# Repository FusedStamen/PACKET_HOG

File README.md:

# PACKET_HOG

10-node ESP32-C5 scanner carrier board. One master, a bank of scan nodes, single USB-C power in.

Status: **PacketHog-V2 first batch is sold out. A restock order has been placed** (no firm arrival date, no preorders; the store page reopens when boards are in hand). V1 (first batch of 8) is also sold out. Every V2 board is assembled and checked before it ships.

## What it is

Packet Hog C5 is a carrier board built around the Seeed XIAO ESP32-C5. One master node coordinates a bank of scanner nodes over ESP-NOW, each scanning dual-band Wi-Fi (2.4/5 GHz) and BLE. The whole array runs off a single USB-C input.

Built deliberately barebones with power distribution, node bank, antenna breakout, nothing else.

Board size: 183.7mm x 121.1mm (7.23 x 4.77 in), 1.6mm thick. Standard case: 188.1mm x 125.5mm, about 29mm tall. Fan case: about 45.5mm tall.

## Buy it

PacketHog-V2: **$100**, shipping to the US only right now. Same price for every option. **Currently sold out, restock ordered.** Restock alert signup: [tally.so/r/Z9Elga](https://tally.so/r/Z9Elga)

[fusedstamen.com/packethogv2](https://fusedstamen.com/packethogv2)

Options at checkout when available: soldered RP-SMA connectors, or bare board (as received from assembly, SMA positions empty). Every board comes with the standard printed case. A case with a 30mm fan opening is available to print from this repo if you want one. Name and Discord are optional at checkout; I only need a shipping address and email.

Modules (Seeed XIAO ESP32-C5), antennas and fan not included. Outside the US, message me on Discord first - import VAT, duties and carrier fees are paid by the buyer on delivery.

## Case hardware

- Standard case: 4x M3x25 screws into M3 heat-set inserts.
- Fan case lid: 4x M3x40 (about 2.5mm of thread engagement; use M3x45 if it feels loose).
- Fan: 5V, 2-pin, 30mm. Check the fan thickness against the fan case. Fan screws are 2-4x M3x8 to M3x10 self-tapping. Specific fans are untested.

**Note on the RP-SMA connectors (J1-J10):** they're mounted to the board for physical support only - there's no PCB trace routing antenna signal to them. Each node module's signal reaches its SMA connector through a short U.FL-to-RP-SMA pigtail from the module itself, not through the board's copper. Same setup as the Piglet, in case that's caused confusion before.

**Mounting orientation:** every header position follows the same rule. Seat each XIAO module so its USB-C port faces the same side as the nearby capacitor (e.g. C11 sits next to the H1A/H1B pair) - that side matches the direction the onboard USB-C (J11) faces. The module's U.FL antenna pad ends up on the opposite side. Get this backwards and the module won't seat or power on correctly; double check before powering on.

## Version history

- **Prototype 1** - First routed prototype. Had a wiring mistake around the CH224K USB-C PD negotiation chip: on a "smart" PD-negotiating charger, the board could get handed the wrong voltage, which risked damaging the nodes. Safe with plain 5V "dumb" chargers only.
- **Prototype 2** - CH224K removed entirely; replaced with 5.1kΩ pull-down resistors on CC1/CC2, forcing 5V-default behavior regardless of charger. Also added reverse-polarity protection, a fuse at the power input, bulk + per-node decoupling capacitors, and 10 edge-mounted SMA connectors for external antennas. Had a layout flaw: SMA connector mounts sat too close to the header pins, leaving insufficient clearance to hand-solder/route pigtail connections without crowding the header footprints. Also shipped without mounting holes, so boards couldn't be securely fastened into a case.
- **PacketHog-V1** - Fixes the clearance flaw by widening the board (77.1mm to 121.1mm) to give proper spacing between the SMA connectors and the header rows. Added M3 mounting holes. Rounded board corners. SMA connectors hand-soldered (not PCBA-populated). First batch of 8 sold out.
- **PacketHog-V2** - Current revision. Power traces widened from 0.5mm to 1.0mm (the USB-C-to-fuse run is limited by the connector pad width). Added a 2-pin fan header (5V + GND, factory assembled). Added an AUX 5V/GND through-hole header, unpopulated, same pinout as the fan header (square pad GND, round pad +5V). Added 7 labelled test points: USB input voltage, between fuse and diode, 5V rail, far-end 5V, and 3x GND. Silkscreen cleanup; back label says V2. Power parts unchanged from V1. Still hand-soldered through-hole RP-SMA (mechanical only), plain USB-C 5V with no PD, 3A maximum (PTC fuse, fan counts against it).
- **Planned for V3** - Power switch, power LED, onboard U.FL plus edge SMA, battery input, possibly 4-layer.

**Known issue:** some nodes drop out with certain off-brand USB cables or power banks. Cause not yet measured; V2 does not claim to fix it. Use a decent USB-C cable and a supply that can deliver 5V at 3A.

## Status of what's tested

| Component | Status |
|---|---|
| Power distribution | Tested |
| Fully populated board scanning | Tested |
| PacketHog-V1 board fab/assembly | Tested |
| PacketHog-V2 board fab/assembly | Tested (each board checked before shipping) |
| Fan case (30mm) | Complete, files in this repo |
| Antenna path (module -> U.FL/SMA pigtail) | Tested |

## Thermal notes

I ran a thermal test on a V1 board in a closed case in a room at about 78F (25.5C). After 75+ minutes of running, the air inside the case levelled off around 96F (36C) and the nodes measured about 102-110F (39-43C) with a thermocouple. An IR thermometer read higher, 108-118F (42-48C), which is typical of IR on shiny surfaces, so treat the thermocouple numbers as the more reliable set. The test was on V1; V2 uses the same power parts with wider copper.

For reference, Espressif rates the ESP32-C5 modules for an operating ambient temperature of -40C to 85C (185F). The Seeed XIAO ESP32-C5 board is listed at 0C to 85C. Nodes ran well inside that range in my test, so I don't think a fan is necessary. The fan header and fan case are there if you want extra airflow or plan to run in a hot environment, such as a car parked in the sun. Those limits are ambient ratings, so a very hot environment leaves less margin.

Test data: [Packet_Hog-v1-Thermal_Testing.xlsx](./Packet_Hog-v1-Thermal_Testing.xlsx)

## License

Licensed under **CC BY-NC 4.0** - see [LICENSE](./LICENSE) for full terms.

Short version: you're free to build one for yourself and modify it for personal, non-commercial use. Selling anything built from this design - boards, kits, or products - requires explicit permission from me first. See the LICENSE file for exactly what that means.

## Contact

- Discord: `Fusedstamen`
- GitHub: [github.com/FusedStamen](https://github.com/FusedStamen)

If you want to use this commercially, reach out through one of the above. Don't assume permission - wait for a yes.

## Name

"Packet Hog" - a reference to [Bilmuri](https://bilmuri.com), not a fork or rename of anyone else's project.

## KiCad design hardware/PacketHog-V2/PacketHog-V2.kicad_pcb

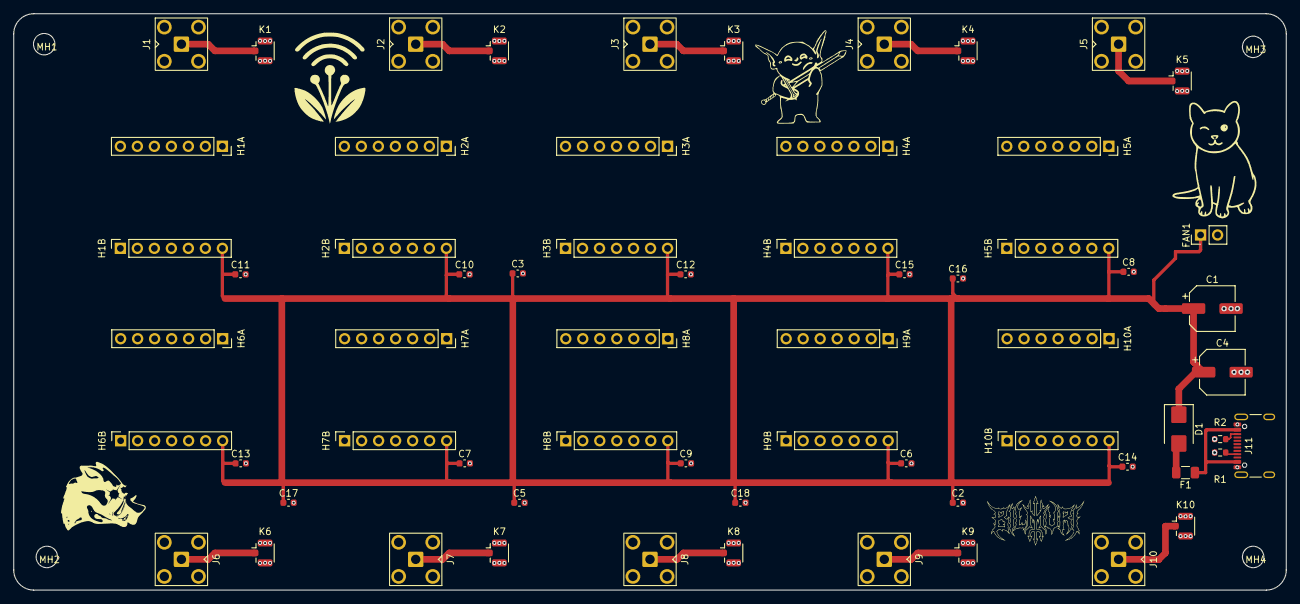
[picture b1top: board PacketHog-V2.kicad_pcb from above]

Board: 2 copper layers, 190.1 x 86.1 mm, 68 parts (0 on the bottom side), 16 nets.

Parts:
C1, C4: CP_Elec_6.3x5.4
C2, C3, C5, C16, C17, C18: 1uF; C_0603_1608Metric
C6, C7, C8, C9, C10, C11, C12, C13, C14, C15: 10uF; C_0603_1608Metric
D1: D_SMB
F1: Fuse_1206_3216Metric
FAN1: PinHeader_1x02_P2.54mm_Vertical
H1A, H1B, H2A, H2B, H3A, H3B, H4A, H4B, H5A, H5B, H6A, H6B, H7A, H7B, H8A, H8B, H9A, H9B, H10A, H10B: PinSocket_1x07_P2.54mm_Vertical
J1, J2, J3, J4, J5, J6, J7, J8, J9, J10: SMA_BAT_Wireless_BWSMA-KWE-Z001
J11: USB_C_Receptacle_GCT_USB4105; USB_C_Receptacle_GCT_USB4105-xx-A_16P_TopMnt_Horizontal
K1, K2, K3, K4, K5, K6, K7, K8, K9, K10: U.FL_Hirose_U.FL-R-SMT-1_Vertical
MH1, MH2, MH3, MH4: MountingHole_3.2mm_M3
R1, R2: 5.1k; R_0603_1608Metric

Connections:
+5V: C1.1, C2.1, C3.1, C4.1, C5.1, C6.1, C7.1, C8.1, C9.1, C10.1, C11.1, C12.1, C13.1, C14.1, C15.1, C16.1, C17.1, C18.1, D1.1, FAN1.1, H1B.7, H2B.7, H3B.7, H4B.7, H5B.7, H6B.7, H7B.7, H8B.7, H9B.7, H10B.7
CC1: J11.B5, R2.2
CC2: J11.A5, R1.2
F1_OUT: D1.2, F1.2
GND: C1.2, C2.2, C3.2, C4.2, C5.2, C6.2, C7.2, C8.2, C9.2, C10.2, C11.2, C12.2, C13.2, C14.2, C15.2, C16.2, C17.2, C18.2, FAN1.2, H1B.6, H2B.6, H3B.6, H4B.6, H5B.6, H6B.6, H7B.6, H8B.6, H9B.6, H10B.6, J1.2, J2.2, J3.2, J4.2, J5.2, J6.2, J7.2, J8.2, J9.2, J10.2, J11.A1, J11.A12, J11.B1, J11.B12, J11.SH, K1.2, K2.2, K3.2, K4.2, K5.2, K6.2, K7.2, K8.2, K9.2, K10.2, R1.1, R2.1
SMA1: J1.1, K1.1
SMA2: J2.1, K2.1
SMA3: J3.1, K3.1
SMA4: J4.1, K4.1
SMA5: J5.1, K5.1
SMA6: J6.1, K6.1
SMA7: J7.1, K7.1
SMA8: J8.1, K8.1
SMA9: J9.1, K9.1
SMA10: J10.1, K10.1
VBUS: F1.1, J11.A4, J11.A9, J11.B4, J11.B9

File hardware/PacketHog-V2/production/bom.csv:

Designator,Footprint,Quantity,Value,LCSC Part #
"C1, C4",CP_Elec_6.3x5.4,2,CP_Elec_6.3x5.4,
"C10, C11, C12, C13, C14, C15, C6, C7, C8, C9",0603,10,10uF,
"C16, C17, C18, C2, C3, C5",0603,6,1uF,
D1,D_SMB,1,D_SMB,
F1,1206,1,Fuse_1206_3216Metric,
FAN1,PinHeader_1x02_P2.54mm_Vertical,1,PinHeader_1x02_P2.54mm_Vertical,
"H10A, H10B, H1A, H1B, H2A, H2B, H3A, H3B, H4A, H4B, H5A, H5B, H6A, H6B, H7A, H7B, H8A, H8B, H9A, H9B",PinSocket_1x07_P2.54mm_Vertical,20,PinSocket_1x07_P2.54mm_Vertical,
"J1, J10, J2, J3, J4, J5, J6, J7, J8, J9",SMA_BAT_Wireless_BWSMA-KWE-Z001,10,SMA_BAT_Wireless_BWSMA-KWE-Z001,
J11,USB_C_Receptacle_GCT_USB4105-xx-A_16P_TopMnt_Horizontal,1,USB_C_Receptacle_GCT_USB4105,
"K1, K10, K2, K3, K4, K5, K6, K7, K8, K9",U.FL_Hirose_U.FL-R-SMT-1_Vertical,10,U.FL_Hirose_U.FL-R-SMT-1_Vertical,
"R1, R2",0603,2,5.1k,

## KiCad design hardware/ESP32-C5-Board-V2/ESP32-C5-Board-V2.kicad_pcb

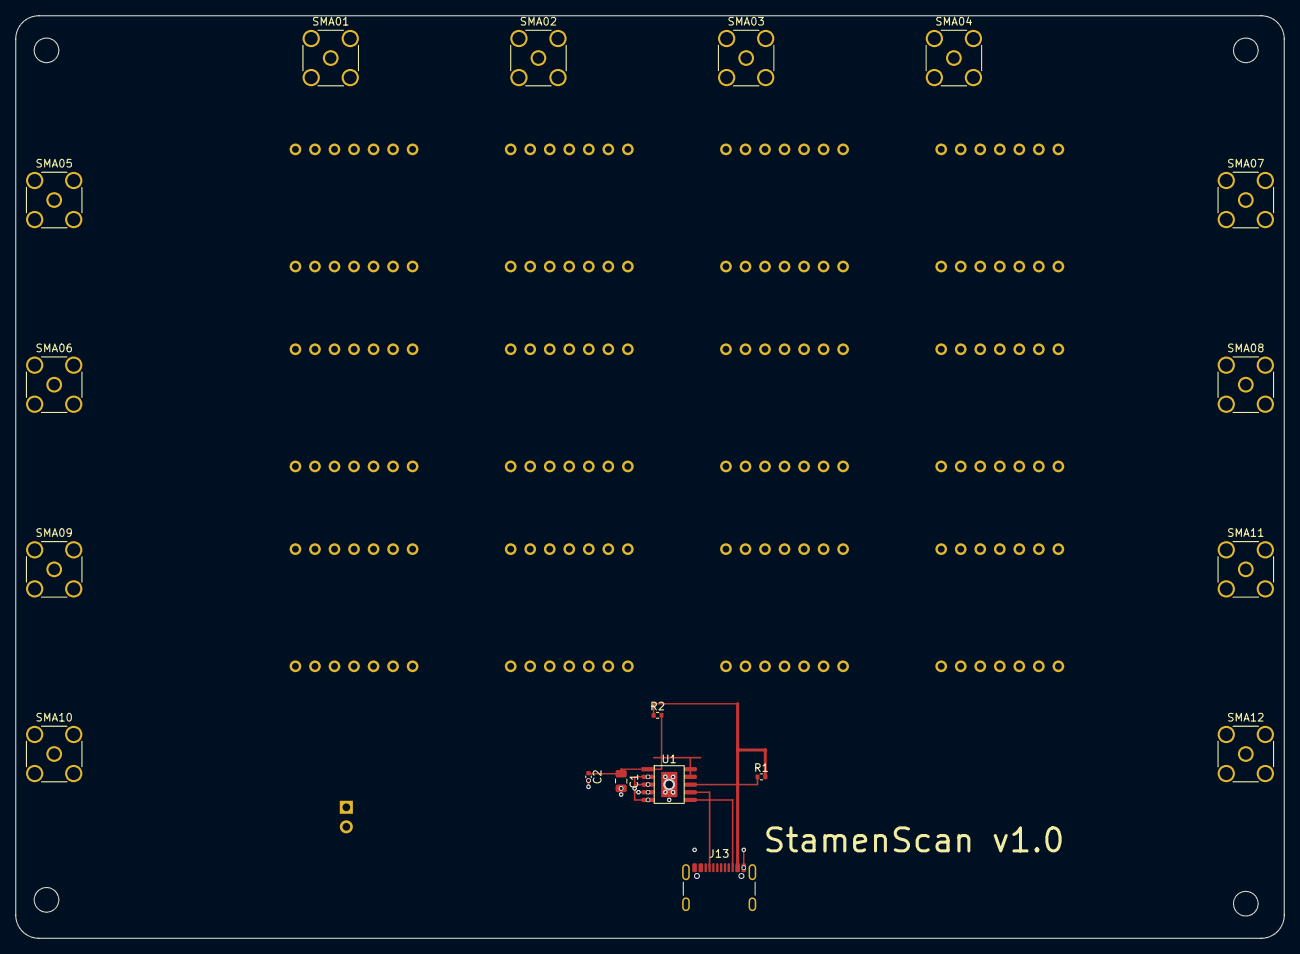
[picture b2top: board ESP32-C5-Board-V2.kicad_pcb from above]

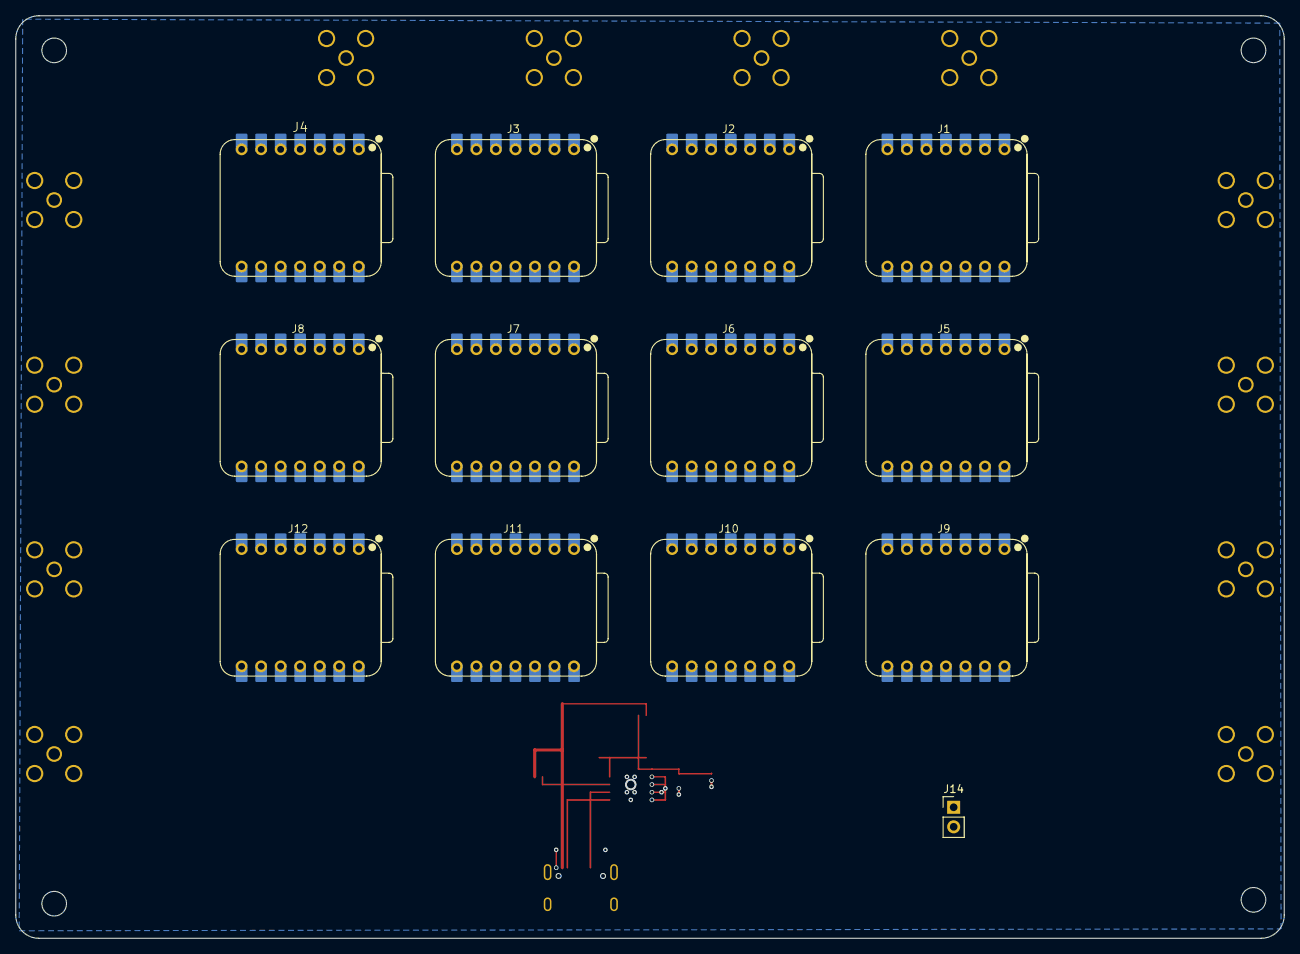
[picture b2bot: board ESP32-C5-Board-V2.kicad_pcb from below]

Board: 2 copper layers, 165.0 x 120.0 mm, 35 parts (17 on the bottom side), 5 nets.

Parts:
C1: 100nF; C_0805_2012Metric
C2: 10uF; C_0402_1005Metric
J1, J2, J3, J4, J5, J6, J7, J8, J9, J10, J11, J12: XIAO-ESP32-C5; XIAO-ESP32-C5-DIP
J13: USB_C_PWR_IN; USB_C_Receptacle_GCT_USB4105-xx-A_16P_TopMnt_Horizontal
J14: FAN; PinHeader_1x02_P2.54mm_Vertical
MH1, MH2, MH3, MH4: MountingHole_3.2mm
R1: 10k; R_0402_1005Metric
R2: 1k; R_0402_1005Metric
SMA01, SMA02, SMA03, SMA04, SMA05, SMA06, SMA07, SMA08, SMA09, SMA10, SMA11, SMA12: SMA_Amphenol_132291_Vertical
U1: CH224K; CH224K_ESSOP-10

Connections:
+5V: J1.14 (VBUS), J2.14 (VBUS), J3.14 (VBUS), J4.14 (VBUS), J5.14 (VBUS), J6.14 (VBUS), J7.14 (VBUS), J8.14 (VBUS), J9.14 (VBUS), J10.14 (VBUS), J11.14 (VBUS), J12.14 (VBUS), J13.A4, J13.A9, J13.B4, J13.B9, J14.1 (+5V), R1.1, R1.2, R2.1, U1.8
CC1: J13.A5 (CC1), U1.7
CC2: J13.B5 (CC2), U1.6
GND: C1.2, C2.2, J1.13 (GND), J2.13 (GND), J3.13 (GND), J4.13 (GND), J5.13 (GND), J6.13 (GND), J7.13 (GND), J8.13 (GND), J9.13 (GND), J10.13 (GND), J11.13 (GND), J12.13 (GND), J13.A1 (VBUS), J13.A12 (GND), J13.B1 (VBUS), J13.B12 (GND), J14.2 (GND), U1.0, U1.2, U1.3, U1.4, U1.5
VDD: C1.1, C2.1, R2.2, U1.1, U1.9, U1.10

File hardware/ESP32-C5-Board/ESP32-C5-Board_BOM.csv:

value,footprint,quantity,references
10k,Resistor_SMD:R_0402_1005Metric,3,"['R1', 'R2', 'R3']"
FAN,Connector_PinHeader_2.54mm:PinHeader_1x02_P2.54mm_Vertical,1,['J14']
100nF,Capacitor_SMD:C_0402_1005Metric,1,['C1']
XIAO-ESP32-C5,XIAO_ESP32:XIAO-ESP32-C5-DIP,12,"['J1', 'J12', 'J4', 'J8', 'J2', 'J10', 'J6', 'J9', 'J3', 'J11', 'J5', 'J7']"
MountingHole_3.2mm,MountingHole:MountingHole_3.2mm,4,"['MH1', 'MH3', 'MH4', 'MH2']"
10uF,Capacitor_SMD:C_0402_1005Metric,1,['C2']
USB_C_PWR_IN,Connector_USB:USB_C_Receptacle_GCT_USB4105-xx-A_16P_TopMnt_Horizontal,1,['J13']
CH224K,Package_SO:SOIC-8_3.9x4.9mm_P1.27mm,1,['U1']

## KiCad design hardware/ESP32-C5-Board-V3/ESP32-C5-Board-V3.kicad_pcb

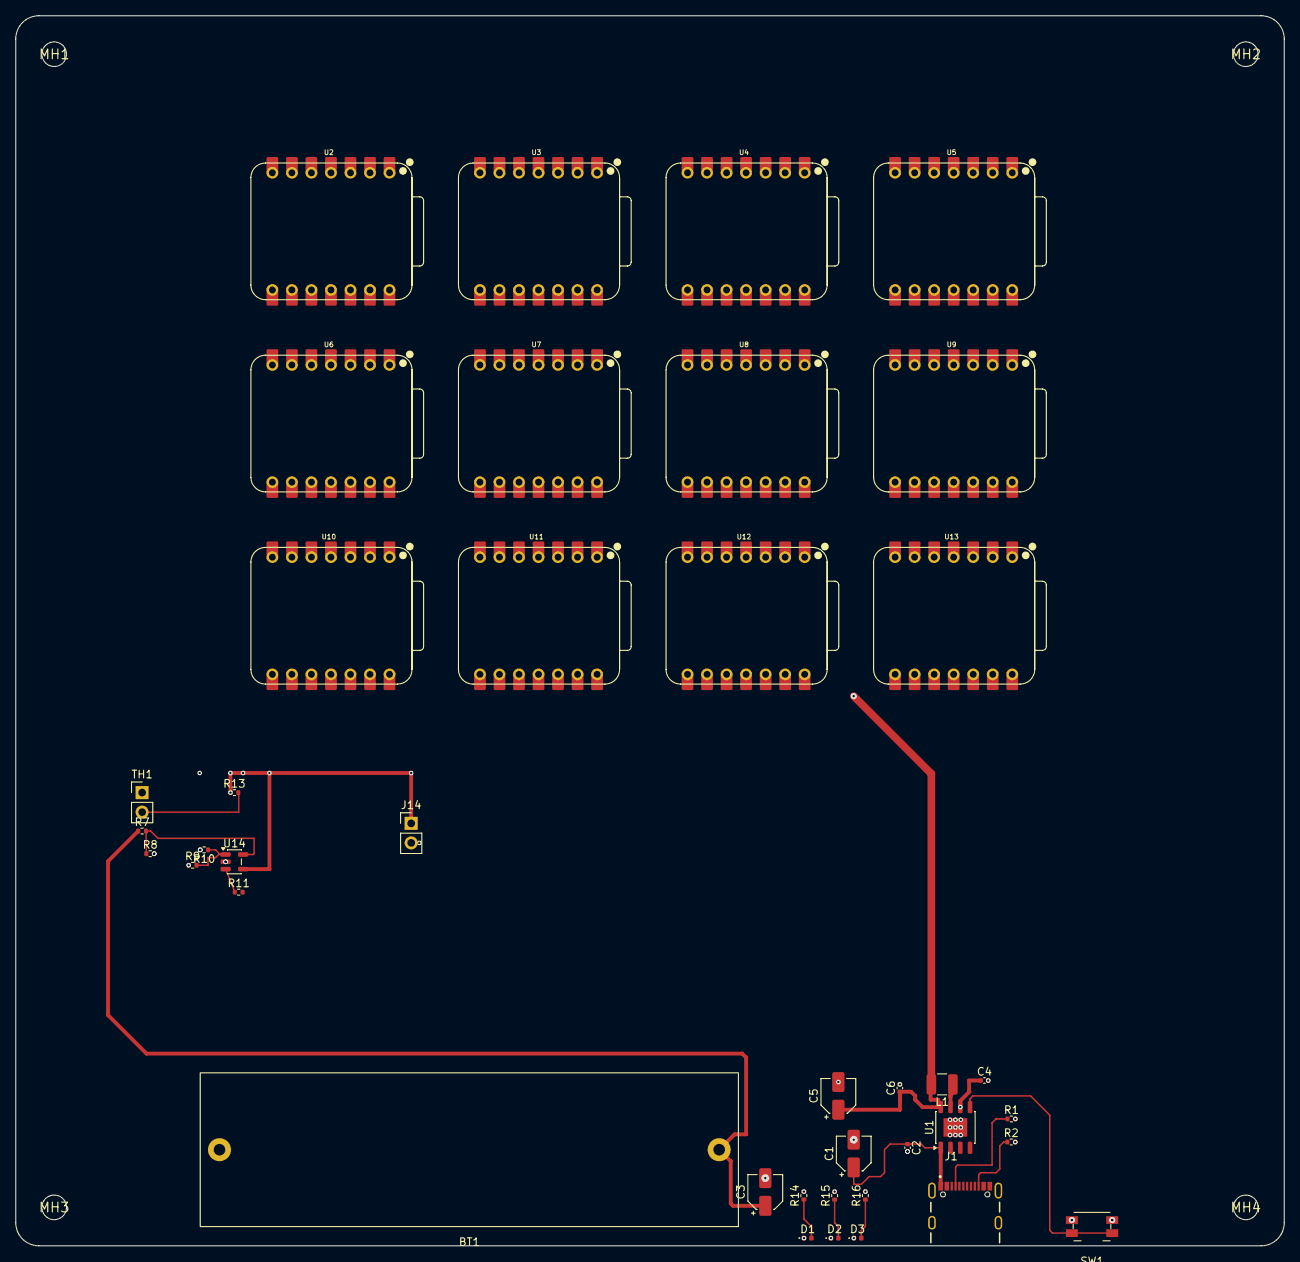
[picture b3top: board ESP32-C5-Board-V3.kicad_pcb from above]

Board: 4 copper layers, 165.0 x 160.0 mm, 44 parts (0 on the bottom side), 12 nets.

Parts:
BT1: INR18650; 18650_SpringTerminals
C1, C3, C5: 100uF; CP_Elec_4x5.4
C2, C4, C6: 100nF; C_0402_1005Metric
D1, D2, D3: LED; LED_0402_1005Metric
J1: GCT_USB4105
J14: FAN_HDR; PinHeader_1x02_P2.54mm_Vertical
L1: 10uH; L_1210_3225Metric
MH1, MH2, MH3, MH4: MountingHole_3.2mm
R1, R2: 5.1k; R_0402_1005Metric
R7, R8, R10: 100k; R_0402_1005Metric
R9: 200k; R_0402_1005Metric
R11, R13: 10k; R_0402_1005Metric
R14, R15, R16: 100R; R_0402_1005Metric
SW1: PWR_BTN; Panasonic_EVQPUJ_EVQPUA
TH1: KSD9700; PinHeader_1x02_P2.54mm_Vertical
U1: IP5306; HSOP-8-1EP_3.9x4.9mm_P1.27mm_EP2.41x3.1mm
U2, U3, U4, U5, U6, U7, U8, U9, U10, U11, U12, U13: XIAO_ESP32_C5; XIAO-ESP32-C5-TH
U14: MCP6541; SOT-23-5

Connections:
+5V: C5.1, C6.1, J14.1, L1.2, R9.1, R13.1, U1.8, U2.14, U3.14, U4.14, U5.14, U6.14, U7.14, U8.14, U9.14, U10.14, U11.14, U12.14, U13.14, U14.4
BATT_LOW_RAW: R11.1, U14.3
BAT_POS: BT1.1, C3.1, C4.1, R7.1, U1.6
CC1: J1.A5, R1.1
CC2: J1.B5, R2.1
GND: BT1.2, C1.2, C2.2, C3.2, C4.2, C5.2, C6.2, D1.1, D2.1, D3.1, R1.2, R2.2, R8.2, R10.2, SW1.2, TH1.1, U1.9, U2.13, U3.13, U4.13, U5.13, U6.13, U7.13, U8.13, U9.13, U10.13, U11.13, U12.13, U13.13, U14.2
KEY: SW1.1, U1.5
SW_NODE: L1.1, U1.7
THERMAL_WARN: R13.2, TH1.2
USB_VIN: C1.1, C2.1, J1.A1_B12, U1.1
VBAT_DIV: R7.2, R8.1, U14.5
VREF: R9.2, R10.1, U14.1
